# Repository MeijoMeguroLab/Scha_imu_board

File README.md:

# scha_imu_board

## Overview
This package contains ROS driver nodes for Murata sensor products mainly communicate by SPI(Serial Periferal Interface).

supported devices:

 - SCHA63T Series
 - SCHA600 Series

## Building the Environment

1.
To write software to Teensy4.0, use "Arduino IDE" and "Arduino IDE + Teensyduino".
 Please install them on your Windows PC.
  
2.
  Next, place the extracted folder in an appropriate directory.

"SCHA" ⇒ scha IMU library, place it in the arudino library directory by folder.
                      This is the default location ( C:\Program Files (x86)\Arduino\libraries )
                      e.g.) C:\Program Files (x86)\Arduino\libraries\SCHA
                      
Change the valid definitions in SCHA.cpp depending on the platform you are writing to. 

By default, SCHA6xx_x03 is valid.

<br>
"scha_board" ⇒ teensy's working directory.
                      Place it anywhere you want and run scha_board.ino when compiling/writing.

3.
  After placing the folder, double-click scha_board.ino to run it in Arduino IDE.
  Click the verification button (check mark) in the upper left corner to compile the program.
  
  After the compile result is displayed at the bottom of Arduino IDE with no error, click
  Press the Write button on Teensy4.0 once.
  (Teensy 4.0 will restart automatically after writing.)
  
4.
  "Click the Terminal button in the upper right corner of the Arduino IDE to confirm that the data acquisition is successful.

## How to use

The topic name and .yaml file name are "series name"_xxx, so please change them as necessary.
There is no problem if you use them as they are.

1.
 "ros_package/scha_imu_driver" is a ros driver that runs on linux.
 Please install the ros environment on your Linux PC.

2.
Place "ros_package/scha_imu_driver" in any workspace and build it.

3.
Connect the device to your PC, and edit the device in the .yaml file in "ros_package/scha_imu_driver/config" according to the connection status.

4.
Run the appropriate launch for your device from "ros_package/scha_imu_driver/launch".

## License
scha_imu_board is provided under the BSD 3-Clause License.

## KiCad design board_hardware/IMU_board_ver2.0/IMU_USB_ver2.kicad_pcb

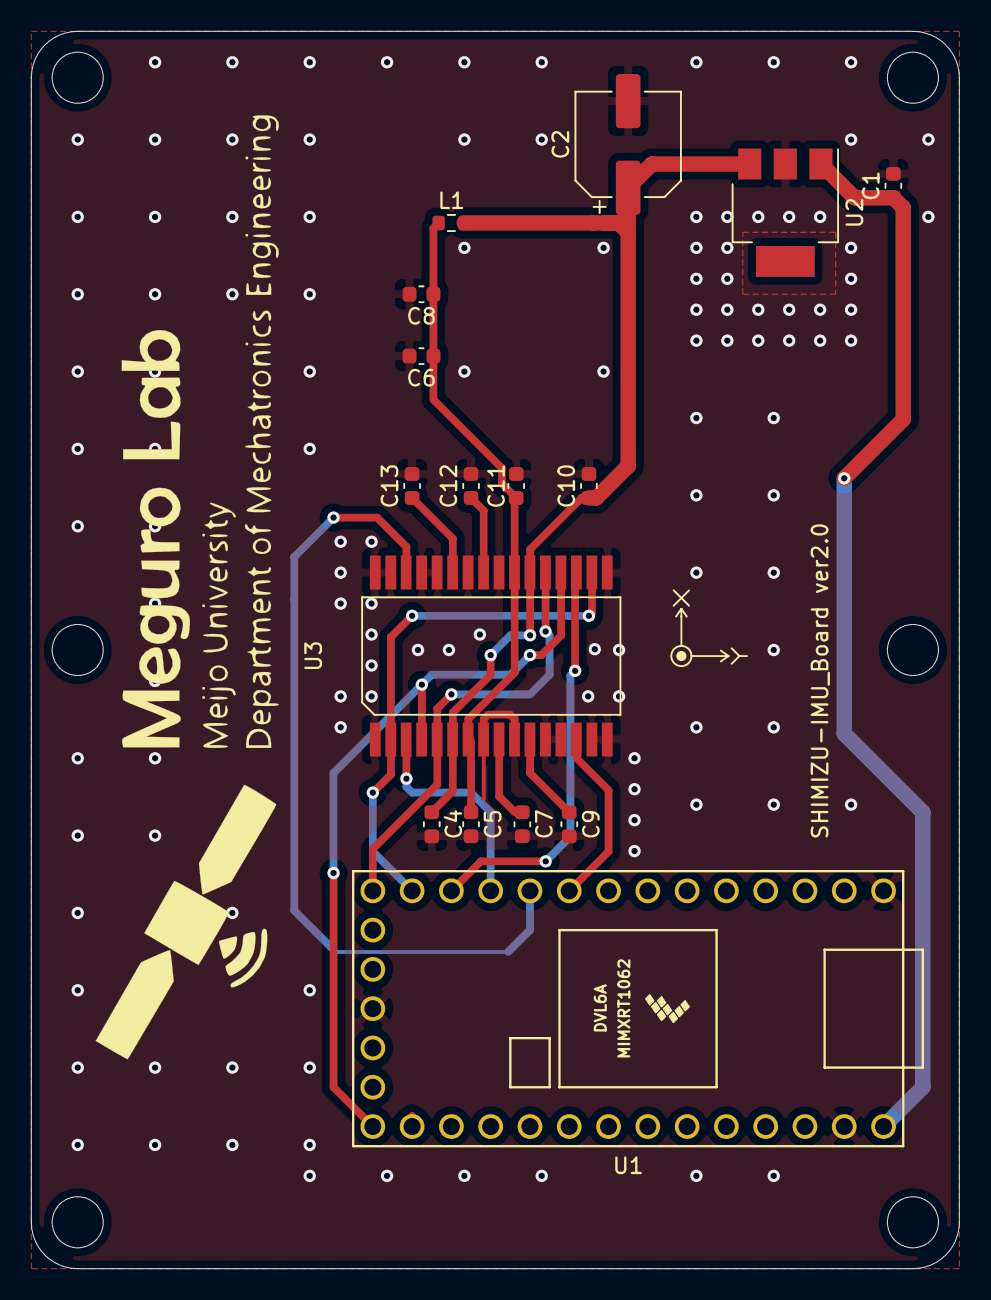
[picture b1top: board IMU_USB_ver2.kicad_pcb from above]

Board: 2 copper layers, 60.0 x 80.0 mm, 16 parts (0 on the bottom side), 15 nets.

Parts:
C1: 1u; C_0603_1608Metric
C2: 22u; CP_Elec_6.3x5.9
C4, C7, C9, C10, C12, C13: 1.5u; C_0603_1608Metric
C5, C11: 0.15u; C_0603_1608Metric
C6: 0.1u; C_0603_1608Metric
C8: 10u; C_0603_1608Metric
L1: BLM15HB121SN1D
U1: Teensy4.0; Teensy40_2
U2: LF33_TO220; SOT-223
U3: SCHA6xx

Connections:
+3.3VA: C5.1, C6.1, C8.1, C11.1, L1.1, U3.7, U3.23
+3V3: C2.1, C4.1, C10.1, L1.2, U2.3, U3.6, U3.22
+5V: C1.1, U1.33, U2.1
CS1: U1.11, U3.3
CS2: U1.12, U3.19
EXTRESN_1: U1.9, U3.14
EXTRESN_2: U1.10, U3.30
GND: C1.2, C2.2, C4.2, C5.2, C6.2, C7.2, C8.2, C9.2, C10.2, C11.2, C12.2, C13.2, U1.1, U1.17, U1.32, U2.2, U3.1, U3.8, U3.10, U3.12, U3.13, U3.15, U3.16, U3.17, U3.24, U3.26, U3.28, U3.29, U3.31, U3.32
MISO_12: U1.14, U3.5, U3.21
MOSI_11: U1.13, U3.2, U3.18
unnamed: C7.1, U3.9
unnamed: C9.1, U3.11
unnamed: C12.1, U3.25
unnamed: C13.1, U3.27
SCK_13: U1.20, U3.4, U3.20

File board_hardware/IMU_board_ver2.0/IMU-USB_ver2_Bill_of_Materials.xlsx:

IMU_board Bill of Materials
No. | value | Unit price[yen] | Quantity(1set) | Purchase unit quantity | URL
C6 | 0.1u | 100 | 1 | 40 | https://akizukidenshi.com/catalog/g/gP-13374/
C5,C11 | 0.15u | 42.26 | 2 | 1 | https://www.marutsu.co.jp/pc/i/26774335/
C1 | 1.0u | 100 | 1 | 20 | https://akizukidenshi.com/catalog/g/gP-14526/
C4,C7,C9,C10,C12,C13 | 1.5u | 67.319999999999993 | 6 | 1 | https://www.marutsu.co.jp/pc/i/27066708/
C8 | 10u | 150 | 1 | 10 | https://akizukidenshi.com/catalog/g/gP-13161/
C2 | 22u | 60 | 1 | 1 | https://akizukidenshi.com/catalog/g/gP-14491/
L1 | BLM18RK121SN1D | 100 | 1 | 25 | https://akizukidenshi.com/catalog/g/gP-04445/
U1 | (Teensy4.0) | 3092 | 1 | 1 | https://www.switch-science.com/catalog/5877/
 | (pin header) | 35 | 28 | 40 | https://akizukidenshi.com/catalog/g/gC-00167/
U2 | LT1963AEST-3.3 | 350 | 1 | 1 | https://akizukidenshi.com/catalog/g/gI-16060/
U3 | SCHA6xx(murata_IMU)
 | ピンソケット | 80 | 28 | 42 | https://akizukidenshi.com/catalog/g/gC-05779/
whithout pin header | (Teensy4.0) | 3092 | 1 | 1 | https://www.switch-science.com/catalog/5877/
 | (pin header) | 35 | 28 | 40 | https://akizukidenshi.com/catalog/g/gC-00167/
with pin header | Teensy4.0(whith pin header) | 3442 | 1 | 1 | https://www.switch-science.com/catalog/6570/

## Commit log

2021-09-21 edit comment
2021-10-07 Added temperature acquisition to ros
